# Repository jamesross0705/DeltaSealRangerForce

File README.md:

ECE 212 Critter Cam Project

This repository is used for keeping track of our schematics, documentation, operation manuals, and models.

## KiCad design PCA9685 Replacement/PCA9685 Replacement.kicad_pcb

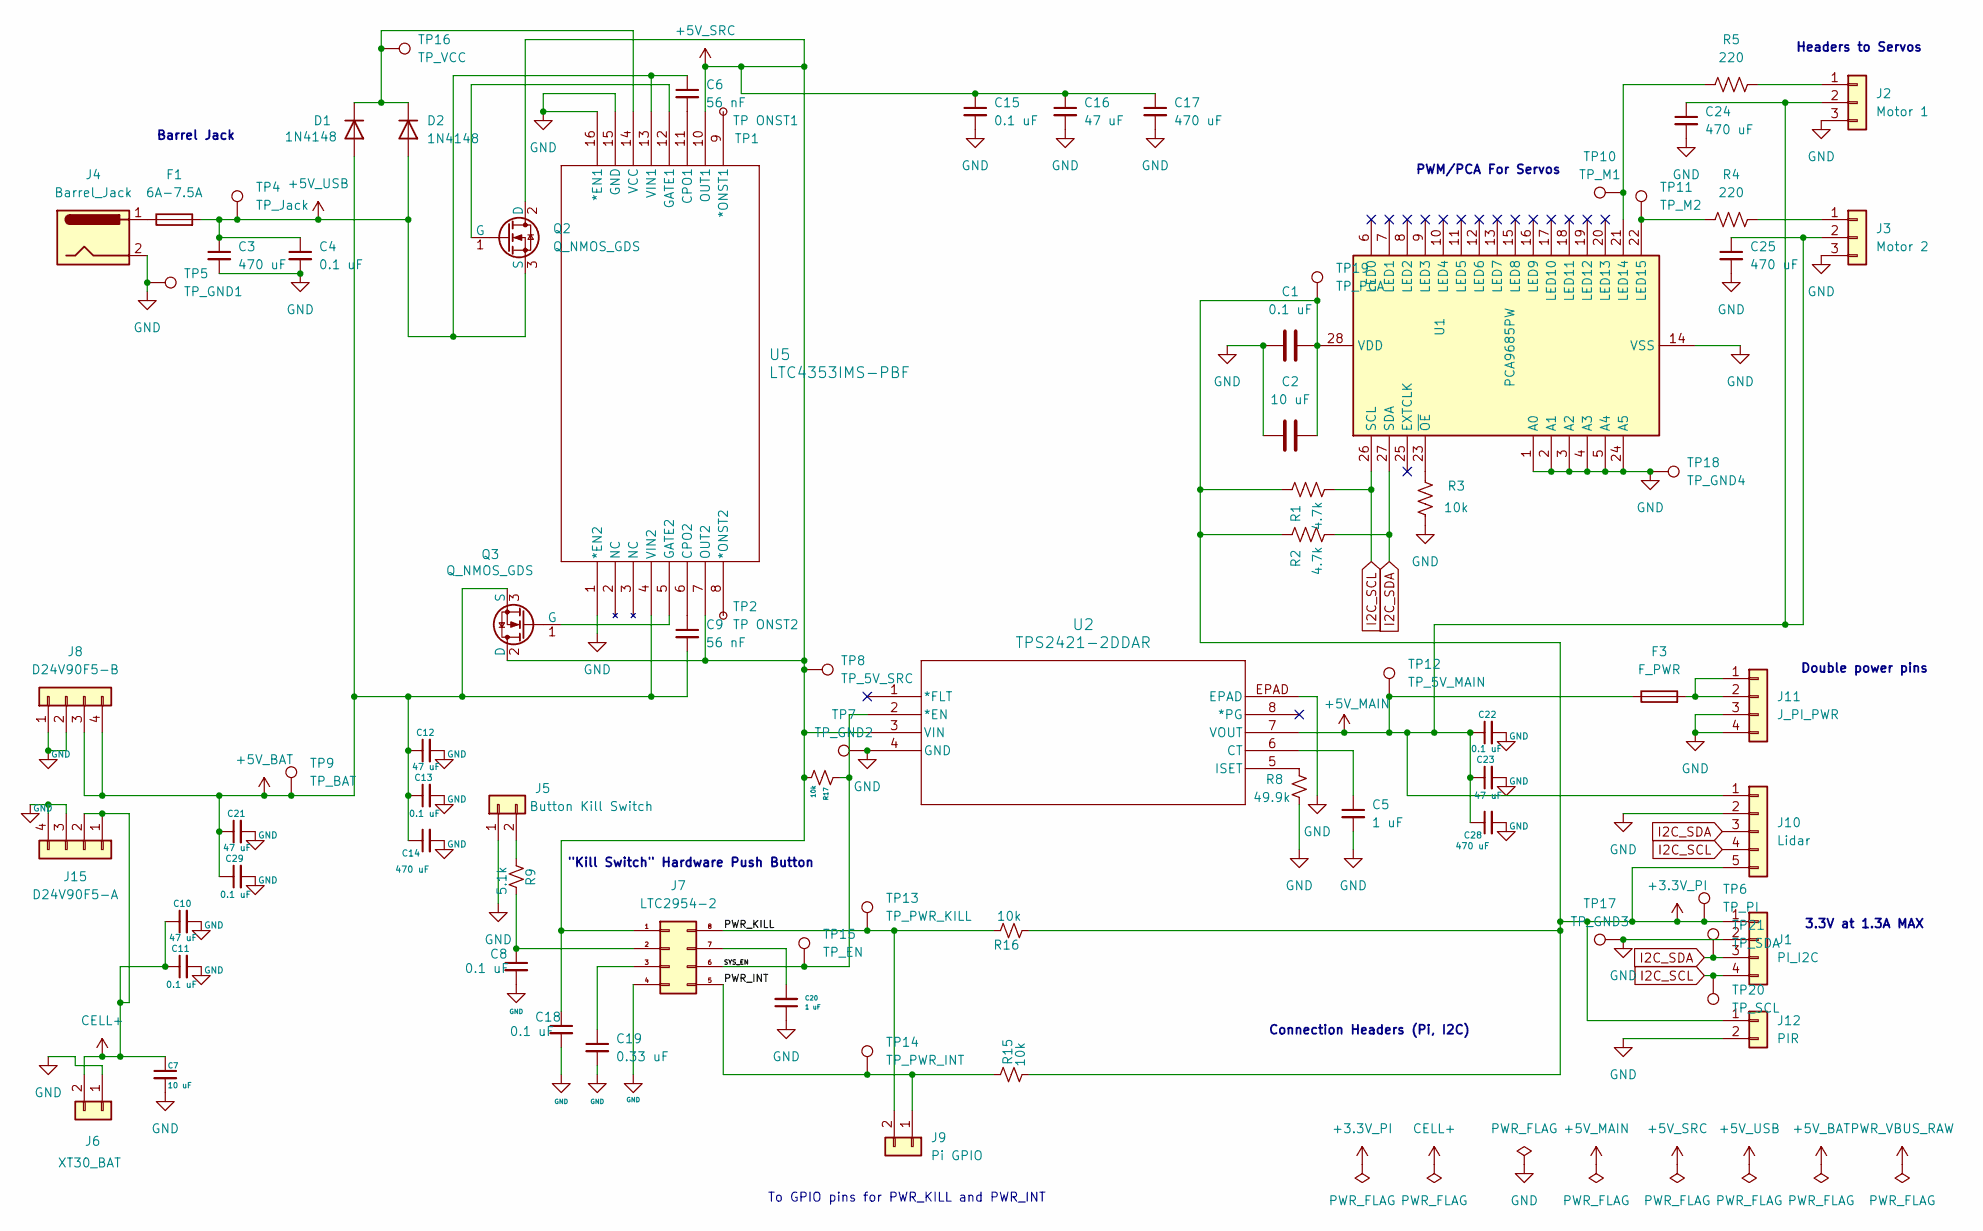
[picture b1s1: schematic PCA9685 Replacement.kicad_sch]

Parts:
C1, C4, C8, C11, C13, C15, C18, C22, C29: 0.1 uF; C_0805_2012Metric
C2, C7: 10 uF; C_0805_2012Metric
C3, C14, C17, C24, C25, C28: 470 uF; CP_Radial_D10.0mm_P5.00mm
C5, C20: 1 uF; C_0805_2012Metric
C6, C9: 56 nF; C_0805_2012Metric
C10, C12, C16, C21, C23: 47 uF; C_1206_3216Metric
C19: 0.33 uF; C_0805_2012Metric
D1, D2: 1N4148; D_DO-35_SOD27_P7.62mm_Horizontal
F1: 6A-7.5A; Fuse_2920_7451Metric_Pad2.10x5.45mm_HandSolder
F3: F_PWR; Fuse_2920_7451Metric_Pad2.10x5.45mm_HandSolder
J1: PI_I2C; PinSocket_1x04_P2.54mm_Vertical
J2: Motor 1; PinSocket_1x03_P2.54mm_Vertical
J3: Motor 2; PinSocket_1x03_P2.54mm_Vertical
J4: Barrel_Jack; BarrelJack_CUI_PJ-102AH_Horizontal
J5: Button Kill Switch; PinSocket_1x02_P2.54mm_Vertical
J6: XT30_BAT; AMASS_XT30PW-F_1x02_P2.50mm_Horizontal
J7: LTC2954-2; SOT-23-8
J8: D24V90F5-B; PinSocket_1x04_P2.54mm_Vertical
J9: Pi GPIO; PinSocket_1x02_P2.54mm_Vertical
J10: Lidar; PinHeader_1x05_P2.54mm_Vertical
J11: J_PI_PWR; PinHeader_1x04_P2.54mm_Vertical
J12: PIR; PinSocket_1x02_P2.54mm_Vertical
J15: D24V90F5-A; PinSocket_1x04_P2.54mm_Vertical
Q2, Q3: Q_NMOS_GDS; PowerPAK_SO-8_Single
R1, R2: 4.7k; R_0805_2012Metric
R3, R15, R16, R17: 10k; R_0805_2012Metric
R4, R5: 220; R_0805_2012Metric
R8: 49.9k; R_0805_2012Metric
R9: 5.1k; R_0805_2012Metric
TP1: TP ONST1; TestPoint_THTPad_D2.0mm_Drill1.0mm
TP2: TP ONST2; TestPoint_THTPad_D2.0mm_Drill1.0mm
TP4: TP_Jack; TestPoint_THTPad_D2.0mm_Drill1.0mm
TP5: TP_GND1; TestPoint_THTPad_D2.0mm_Drill1.0mm
TP6: TP_PI; TestPoint_THTPad_D2.0mm_Drill1.0mm
TP7: TP_GND2; TestPoint_THTPad_D2.0mm_Drill1.0mm
TP8: TP_5V_SRC; TestPoint_THTPad_D2.0mm_Drill1.0mm
TP9: TP_BAT; TestPoint_THTPad_D2.0mm_Drill1.0mm
TP10: TP_M1; TestPoint_THTPad_D2.0mm_Drill1.0mm
TP11: TP_M2; TestPoint_THTPad_D2.0mm_Drill1.0mm
TP12: TP_5V_MAIN; TestPoint_THTPad_D2.0mm_Drill1.0mm
TP13: TP_PWR_KILL; TestPoint_Pad_D1.5mm
TP14: TP_PWR_INT; TestPoint_Pad_D1.5mm
TP15: TP_EN; TestPoint_Pad_D1.5mm
TP16: TP_VCC; TestPoint_THTPad_D2.0mm_Drill1.0mm
TP17: TP_GND3; TestPoint_THTPad_D2.0mm_Drill1.0mm
TP18: TP_GND4; TestPoint_THTPad_D2.0mm_Drill1.0mm
TP19: TP_PCA; TestPoint_THTPad_D2.0mm_Drill1.0mm
TP20: TP_SCL; TestPoint_Pad_D1.5mm
TP21: TP_SDA; TestPoint_Pad_D1.5mm
U1: PCA9685PW; TSSOP-28_4.4x9.7mm_P0.65mm
U2: TPS2421-2DDAR; SOIC-8-1EP_3.9x4.9mm_P1.27mm_EP2.29x3mm
U5: LTC4353IMS-PBF; MSOP-16_3x4.039mm_P0.5mm

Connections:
+3.3V_PI: C1.2, C2.1, J1.1, J10.5, J12.1, R1.1, R2.1, R15.2, R16.1, TP6.1, TP19.1, U1.28 (VDD)
+5V_BAT: C9.2, C12.1, C13.1, C14.1, C21.1, C29.1, D1.2 (A), J8.3, J8.4, Q3.3 (S), TP9.1, U5.4 (VIN2)
+5V_MAIN: C22.1, C23.1, C24.1, C25.1, C28.1, F3.1, J2.2, J3.2, J10.1, TP12.1, U2.7 (VOUT)
+5V_SRC: C15.1, C16.1, C17.1, C18.1, J7.1 (VIN), Q2.2 (D), Q3.2 (D), R17.2, TP8.1, U2.3 (VIN), U5.7 (OUT2), U5.10 (OUT1)
+5V_USB: C3.1, C4.1, C6.1, D2.2 (A), F1.2, Q2.3 (S), TP4.1, U5.13 (VIN1)
/PWR_INT: J7.5 (INT), J9.1, R15.1, TP14.1
/PWR_KILL: J7.8 (KILL), J9.2, R16.2, TP13.1
/SYS_EN: J7.6 (EN), R17.1, TP15.1, U2.2 (*EN)
CELL+: C7.1, C10.1, C11.1, J6.2, J15.1, J15.2
GND: C1.1, C2.2, C3.2, C4.2, C5.2, C7.2, C8.2, C10.2, C11.2, C12.2, C13.2, C14.2, C15.2, C16.2, C17.2, C18.2, C19.2, C20.1, C21.2, C22.2, C23.2, C24.2, C25.2, C28.2, C29.2, J1.2, J2.3, J3.3, J4.2, J5.1, J6.1, J7.4 (GND), J8.1, J8.2, J10.2, J11.3, J11.4, J12.2, J15.3, J15.4, R3.2, R8.2, TP5.1, TP7.1, TP17.1, TP18.1, U1.1 (A0), U1.2 (A1), U1.3 (A2), U1.4 (A3), U1.5 (A4), U1.14 (VSS), U1.24 (A5), U2.4 (GND), U2.EPAD, U5.1 (*EN2), U5.15 (GND), U5.16 (*EN1)
I2C_SCL: J1.4, J10.4, R1.2, TP20.1, U1.26 (SCL)
I2C_SDA: J1.3, J10.3, R2.2, TP21.1, U1.27 (SDA)
unnamed: D1.1 (K), D2.1 (K), TP16.1, U5.14 (VCC)
unnamed: F1.1, J4.1
unnamed: J2.1, R5.2
unnamed: J3.1, R4.2
unnamed: J5.2, R9.1
unnamed: C19.1, J7.3 (ONT)
unnamed: C8.1, J7.2 (PB), R9.2
unnamed: C20.2, J7.7 (PDT)
unnamed: F3.2, J11.1, J11.2
unnamed: Q2.1 (G), U5.12 (GATE1)
unnamed: Q3.1 (G), U5.5 (GATE2)
unnamed: R5.1, TP10.1, U1.21 (LED14)
unnamed: R4.1, TP11.1, U1.22 (LED15)
unnamed: R3.1, U1.23 (~OE)
unnamed: C5.1, U2.6 (CT)
unnamed: R8.1, U2.5 (ISET)
unnamed: TP1.1, U5.9 (*ONST1)
unnamed: TP2.1, U5.8 (*ONST2)
unnamed: C6.2, U5.11 (CPO1)
unnamed: C9.1, U5.6 (CPO2)

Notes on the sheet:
To GPIO pins for PWR_KILL and PWR_INT
Headers to Servos
Connection Headers (Pi, I2C)
"Kill Switch" Hardware Push Button
3.3V at 1.3A MAX
Barrel Jack
Double power pins
PWM/PCA For Servos

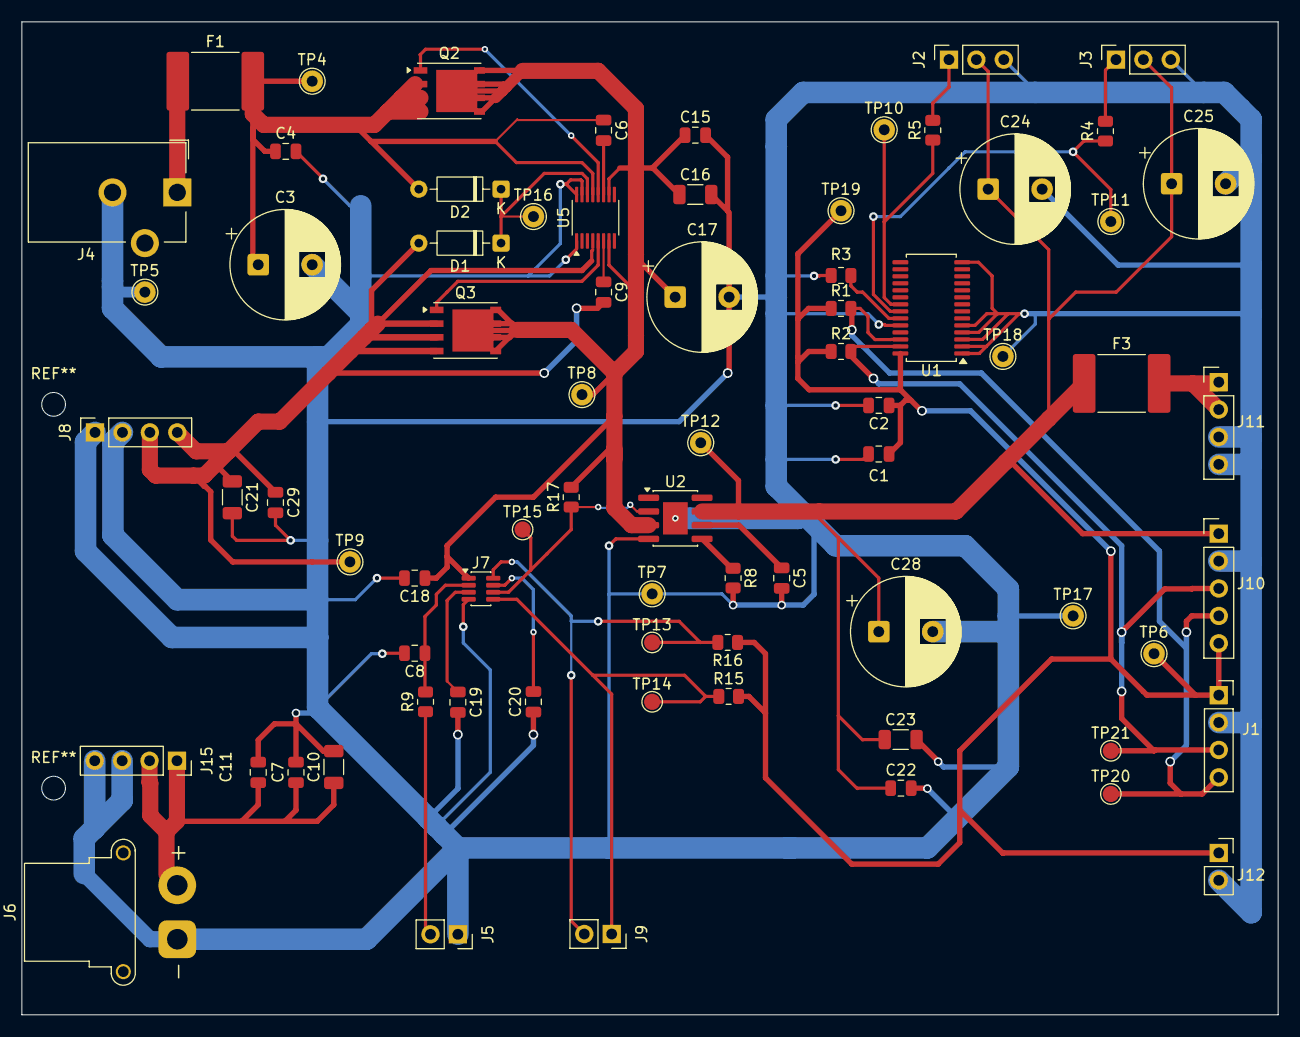
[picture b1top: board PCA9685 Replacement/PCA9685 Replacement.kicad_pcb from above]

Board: 2 copper layers, 116.4 x 92.0 mm, 74 parts (0 on the bottom side), 30 nets.

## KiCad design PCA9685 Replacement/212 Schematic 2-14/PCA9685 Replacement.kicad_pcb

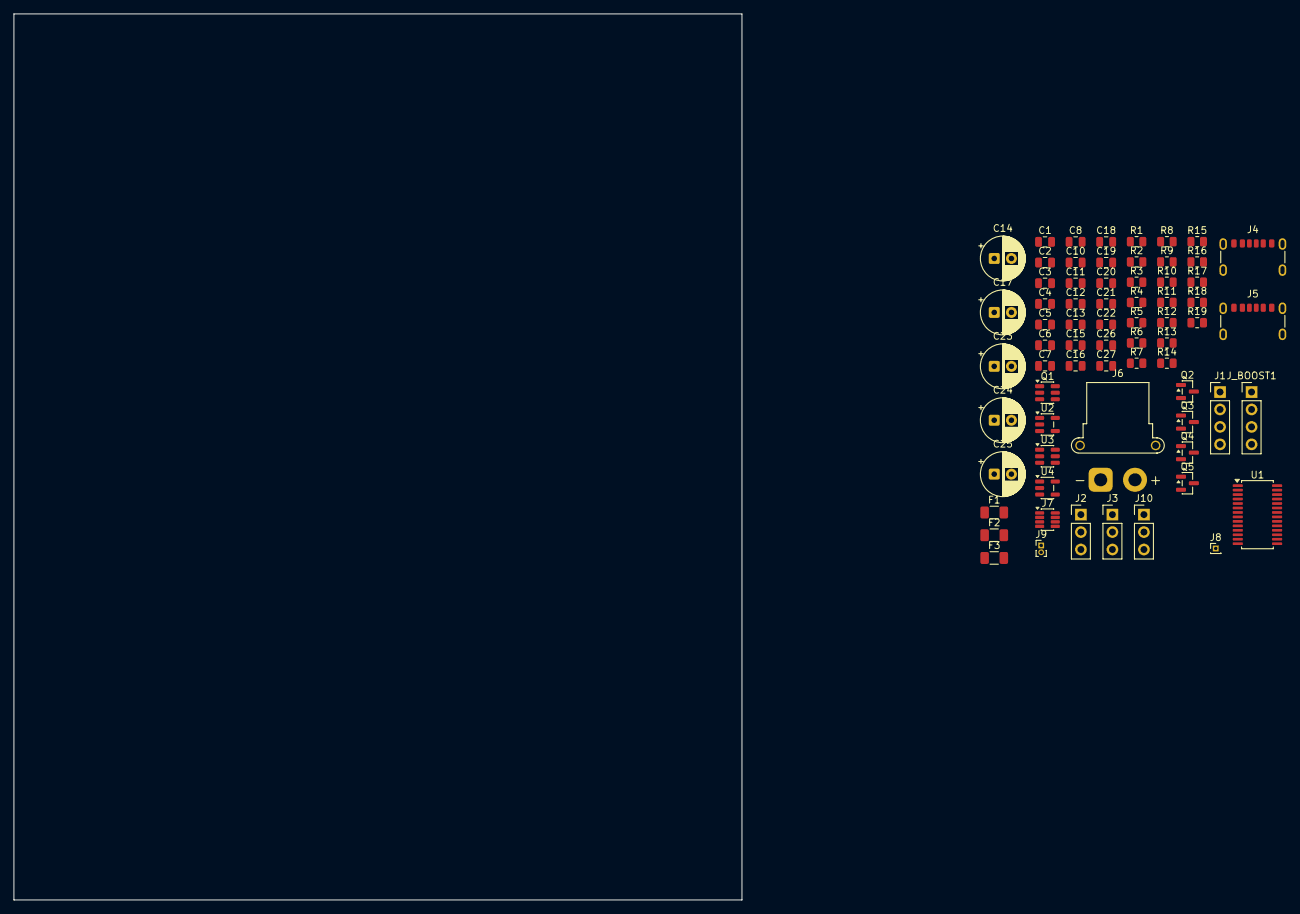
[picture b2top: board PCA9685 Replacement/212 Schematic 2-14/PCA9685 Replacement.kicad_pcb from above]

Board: 2 copper layers, 106.0 x 129.0 mm, 68 parts (0 on the bottom side), 37 nets, no tracks yet.

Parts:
C1, C4, C6, C8, C10, C13, C15, C18, C21: 0.1 uF; C_0805_2012Metric
C2, C7, C26, C27: 10 uF; C_0805_2012Metric
C3, C5, C11: 22 uF; C_0805_2012Metric
C12, C16, C22: 47 uF; C_0805_2012Metric
C14, C17, C23, C24, C25: 470 uF; CP_Radial_D6.3mm_P2.50mm
C19: 0.33 uF; C_0805_2012Metric
C20: 1 uF; C_0805_2012Metric
F1, F2, F3: F_PWR; Fuse_1206_3216Metric
J1: PI_I2C; PinHeader_1x04_P2.54mm_Vertical
J2: Motor 1; PinHeader_1x03_P2.54mm_Vertical
J3: Motor 2; PinHeader_1x03_P2.54mm_Vertical
J4: USB_C_PWR; USB_C_Receptacle_GCT_USB4125-xx-x-0190_6P_TopMnt_Horizontal
J5: USB_C_CHG; USB_C_Receptacle_GCT_USB4125-xx-x-0190_6P_TopMnt_Horizontal
J6: XT30_BAT; AMASS_XT30PW-F_1x02_P2.50mm_Horizontal
J7: LTC2954; SOT-23-8
J8: PB; PinHeader_1x01_P1.00mm_Vertical
J9: J_PI_POWER; PinHeader_1x02_P1.00mm_Vertical
J10: PI_PWR_CTRL; PinHeader_1x03_P2.54mm_Vertical
J_BOOST1: U3V70F5_MODULE; PinHeader_1x04_P2.54mm_Vertical
Q1: Dual_NMOS_1; SOT-23-6
Q2: Q_USB_OR; SOT-23
Q3: Q_BAT_OR; SOT-23
Q4: Q_MAIN; SOT-23
Q5: Q_NMOS_GDS; SOT-23
R1, R2: 4.7k; R_0805_2012Metric
R3, R15, R19: 10k; R_0805_2012Metric
R4, R5: 220; R_0805_2012Metric
R6, R7, R8, R9: 5.1k; R_0805_2012Metric
R10, R18: 100; R_0805_2012Metric
R11: 1k; R_0805_2012Metric
R12, R13, R14, R16, R17: 100k; R_0805_2012Metric
U1: PCA9685PW; TSSOP-28_4.4x9.7mm_P0.65mm
U2: MCP73831-2-OT; SOT-23-5
U3: DW01A; SOT-23-6
U4: AP2112K-3.3; SOT-23-5

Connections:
/3V3: C1.2, C2.1, C27.1, J1.1, R1.1, R2.1, R15.2, U1.28 (VDD), U4.5 (VOUT)
/5V_BAT: C12.1, C13.1, C14.1, J_BOOST1.3, R13.2
/5V_MAIN: C21.1, C22.1, C23.1, C24.1, C25.1, C26.1, F3.1, J2.2, J3.2, Q4.2 (D), U4.1 (VIN), U4.3 (EN)
/5V_PI: F3.2, J9.1
/5V_SRC: C15.1, C16.1, C17.1, C18.1, J7.1 (VIN), Q2.1 (G), Q2.2 (D), Q4.3 (S), R12.1, R13.1, R14.1, R16.2, R17.2, R18.1
/5V_USB: C3.1, C4.1, F1.2, Q2.3 (S), R14.2
/CELL+: C7.1, C10.2, C11.2, J6.1, J_BOOST1.1, R10.1, U2.3 (V_{BAT})
/CELL-: C7.2, C8.1, J6.2, Q1.1 (S), U3.6 (GND)
/CHG_VBUS: C5.1, C6.1, F2.2, U2.4 (V_{DD})
/CHG_VBUS_RAW: F2.1, J5.A9 (VBUS), J5.B9 (VBUS)
/PWR_INT: J7.5 (INT), J10.1, R15.1
/PWR_KILL: J7.8 (KILL), J10.2, R16.1
/PWR_VBUS_RAW: F1.1, J4.A9 (VBUS), J4.B9 (VBUS)
/SYS_EN: J7.6 (EN), J_BOOST1.4, Q5.1 (G), R17.1
GND: C1.1, C2.2, C3.2, C4.2, C5.2, C6.2, C10.1, C11.1, C12.2, C13.2, C14.2, C15.2, C16.2, C17.2, C18.2, C19.2, C20.2, C21.2, C22.2, C23.2, C24.2, C25.2, C26.2, C27.2, J1.2, J2.3, J3.3, J4.A12 (GND), J4.B12 (GND), J4.S1 (SHIELD), J5.A12 (GND), J5.B12 (GND), J5.S1 (SHIELD), J7.4 (GND), J9.2, J10.3, J_BOOST1.2, Q1.4 (S), Q5.3 (S), R3.2, R6.2, R7.2, R8.2, R9.2, R19.1, U1.1 (A0), U1.2 (A1), U1.3 (A2), U1.4 (A3), U1.5 (A4), U1.14 (VSS), U1.24 (A5), U2.2 (V_{SS}), U4.2 (GND)
I2C_SCL: J1.3, R1.2, U1.26 (SCL)
I2C_SDA: J1.4, R2.2, U1.27 (SDA)
unnamed: J2.1, R5.2
unnamed: J3.1, R4.2
unnamed: J4.A5 (CC1), R6.1
unnamed: J4.B5 (CC2), R7.1
unnamed: J5.A5 (CC1), R8.1
unnamed: J5.B5 (CC2), R9.1
unnamed: C19.1, J7.3 (ONT)
unnamed: J7.2 (PB), J8.1
unnamed: C20.1, J7.7 (PDT)
unnamed: Q1.3 (D), Q1.6 (D), R11.2
unnamed: Q1.2 (G), U3.1 (OD)
unnamed: Q1.5 (G), U3.3 (OC)
unnamed: Q4.1 (G), R12.2
unnamed: Q5.2 (D), R18.2
unnamed: R5.1, U1.21 (LED14)
unnamed: R4.1, U1.22 (LED15)
unnamed: R3.1, U1.23 (~OE)
unnamed: R19.2, U2.5 (PROG)
unnamed: R11.1, U3.2 (CS)
unnamed: C8.2, R10.2, U3.5 (VCC)

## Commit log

2026-02-11 Update README with project title and description
    Added project title and description to README
2026-02-24 Updated with tracing
2026-02-27 Create Critter Cam Housing
2026-02-27 Create temp
